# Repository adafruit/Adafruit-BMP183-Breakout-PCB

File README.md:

## Adafruit BMP183 Breakout PCB (Discontinued)
<a href="http://www.adafruit.com/products/1900"><br/>
Click here to view in the Adafruit shop</a>

Fans of the BMP085/BMP180 will want to take a look at the new BMP183 - an SPI spin on the old familiar classic. This precision sensor from Bosch is the best low-cost sensing solution for measuring barometric pressure and temperature. Because pressure changes with altitude you can also use it as an altimeter!

PCB files for the Adafruit BMP183 Breakout (discontinued). The format is EagleCAD schematic and board layout
- https://www.adafruit.com/product/1900

### License

Adafruit invests time and resources providing this open source design, please support Adafruit and open-source hardware by purchasing products from [Adafruit](https://www.adafruit.com)!

All text above must be included in any redistribution

Designed by Limor Fried/Ladyada for Adafruit Industries.
Creative Commons Attribution/Share-Alike, all text above must be included in any redistribution. 
See license.txt for additional information.

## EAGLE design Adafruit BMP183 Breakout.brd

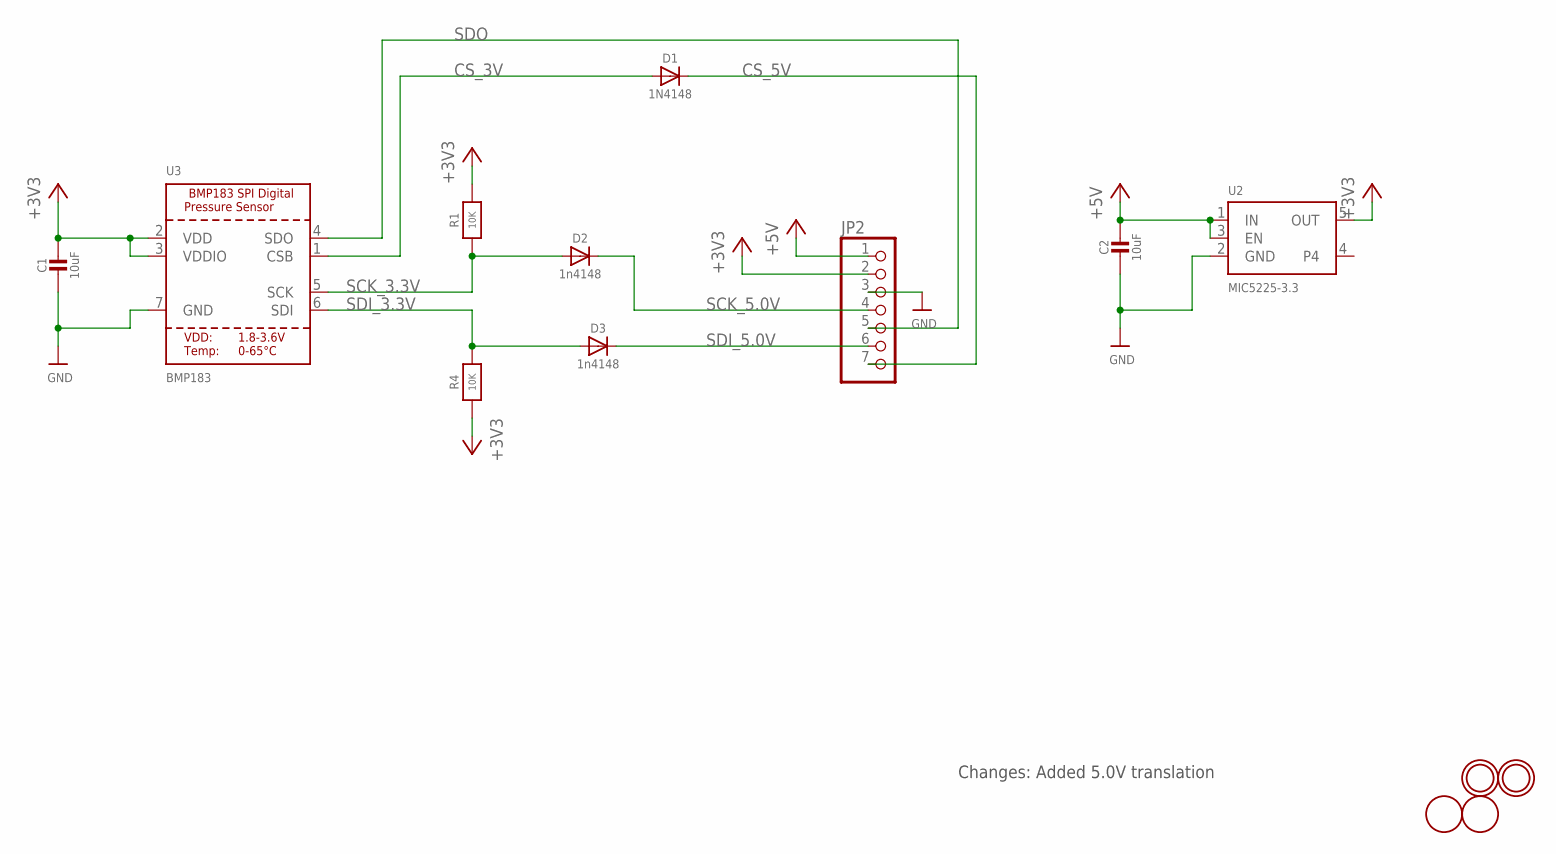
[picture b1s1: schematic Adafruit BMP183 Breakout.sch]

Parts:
C1, C2: 10uF; 0805-NO
D1: 1N4148; SOD-323
D2, D3: 1n4148; SOD-323
JP2: HEADER-1X770MIL; 1X07_ROUND_70
R1, R4: 10K; 0805-NO
U2: MIC5225-3.3; SOT23-5
U3: BMP183; BMP18X_EXTENDED
U$5, U$15: FIDUCIAL; FIDUCIAL_1MM
U$7, U$8: MOUNTINGHOLE2.0; MOUNTINGHOLE_2.0_PLATED

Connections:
+3V3: C1.1, JP2.2, R1.2, R4.1, U2.5 (OUT), U3.2 (VDD), U3.3 (VDDIO)
+5V: C2.1, JP2.1, U2.1 (IN), U2.3 (EN)
CS_3V: D1.A, U3.1 (CSB)
CS_5V: D1.C, JP2.7
GND: C1.2, C2.2, JP2.3, U2.2 (GND), U3.7 (GND)
SCK_3.3V: D2.A, R1.1, U3.5 (SCK)
SCK_5.0V: D2.C, JP2.4
SDI_3.3V: D3.A, R4.2, U3.6 (SDI)
SDI_5.0V: D3.C, JP2.6
SDO: JP2.5, U3.4 (SDO)

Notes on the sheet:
Changes: Added 5.0V translation

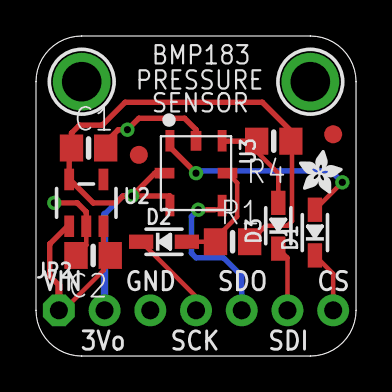
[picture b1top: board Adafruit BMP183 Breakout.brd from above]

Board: 2 copper layers, 17.8 x 17.8 mm, 16 parts (1 on the bottom side), 10 nets.

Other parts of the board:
U$2, U$6: ADAFRUIT_2.5MM

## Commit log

2016-08-24 init
